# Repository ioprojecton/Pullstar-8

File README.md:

# Pullstar-8
I2C 8 Port Servo Driver

The I2C servo driver board by Surepic© is designed to make connecting motors, sensors and other components to your Arduino,Rasberi Pi-based project as fast and easy as possible.

This board allows your Raspberry Pi,Arduino, etc., to control up to 8 servo motors in a simple way via an I2C connection. Thanks to its I2C capabilities, this board saves the Raspberry Pi's,Arduino`s GPIO pins, allowing you to use them for other purposes.

Each of this board's 8 servo motor GPIO pin headers has been spaced out to the standard 3-pin servo pinout (ground, 5V, signal) to make it easier to attach your servo motors and can supply up to 1.25A to each of 8 outputs.

This driver includes headers to connect to a Raspberry Pi,Arduino , so there is no need for soldering to make it up and running.

Using the onboard jumpers for power selection, the input power can be supplied via Arduino's,Rasberi Pi`s regulated voltage, or a completely separate power supply attached to the board's 2.1mm barrel jack. This feature makes this board ideal if you are connecting multiple servos!

Compared to other servo drivers this board offers:
  Independant power control(ON/OFF) to each outputs via i2c.
  Independant duty cycle control to each outputs via i2c.
  Adjustible frequency to up to 1.6khz.
  1.25A per output when powered from external supply.
  LEDs on each output providing feedback if output is ON or OFF.
  2 selectible power sources selectible with jumpers and with led status indicators.
  Onboard voltage regulator (input 6-7v 3A recommended), when barrel jack is used.
  Open collector outputs on power pins.
  I2C addressess are selectable with jumpers for both onboard ics.
  Fully compatible with fast mode I2C 400kbits/s.
  Each board is fully tested before shipping.
  
=========================

Features:

•16 PWM channels, controllable over I2C
•2.1mm industry standard barrel jack port
•Contain an I2C-controlled PWM ic with a built-in clock
•12-bit resolution for each output - for servos(4us at 60hz)
•Controls up to 8 servos
.Dual power inputs (selectible with jumpers).
.Onboard low noise low ripple regulator.
.115 x 105mm size
.Feedback LEDs on each output
.Independant power control to each output

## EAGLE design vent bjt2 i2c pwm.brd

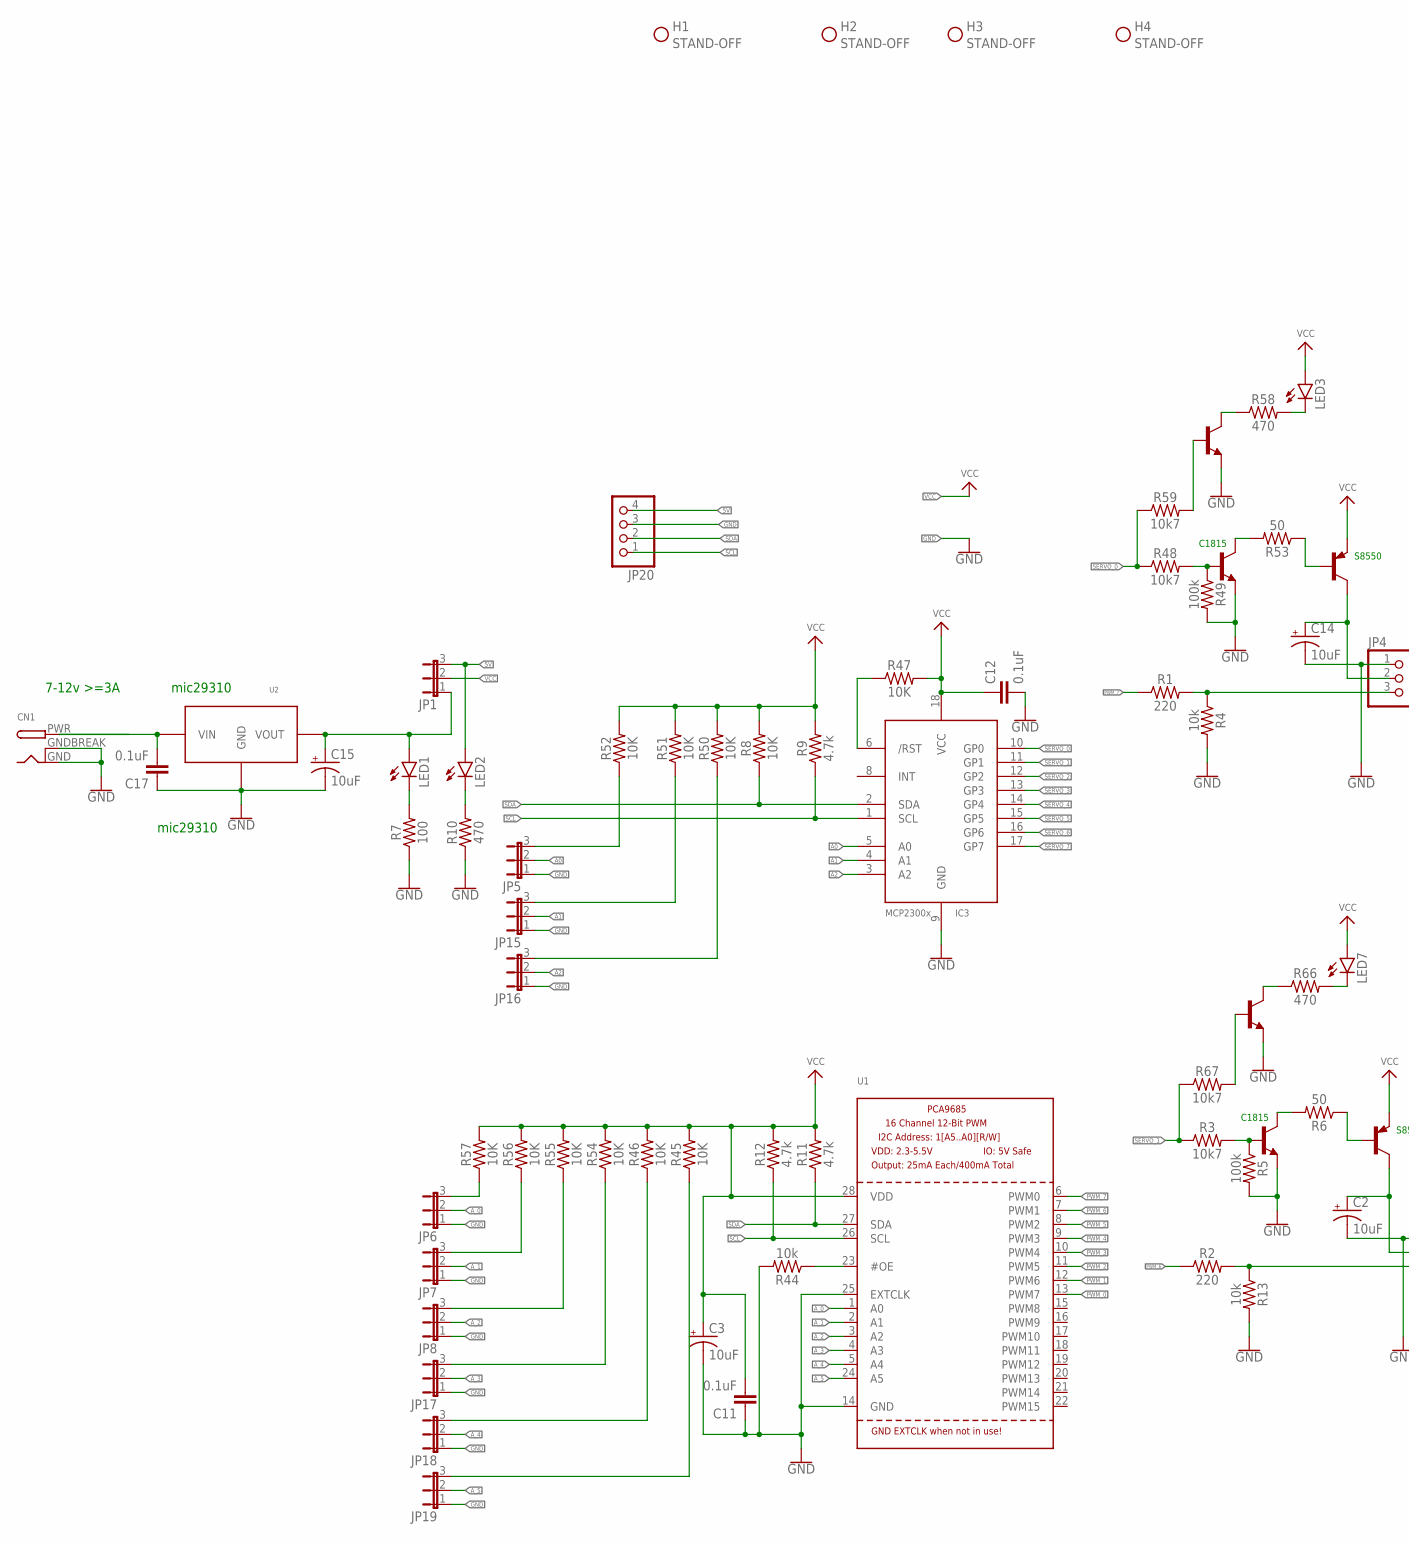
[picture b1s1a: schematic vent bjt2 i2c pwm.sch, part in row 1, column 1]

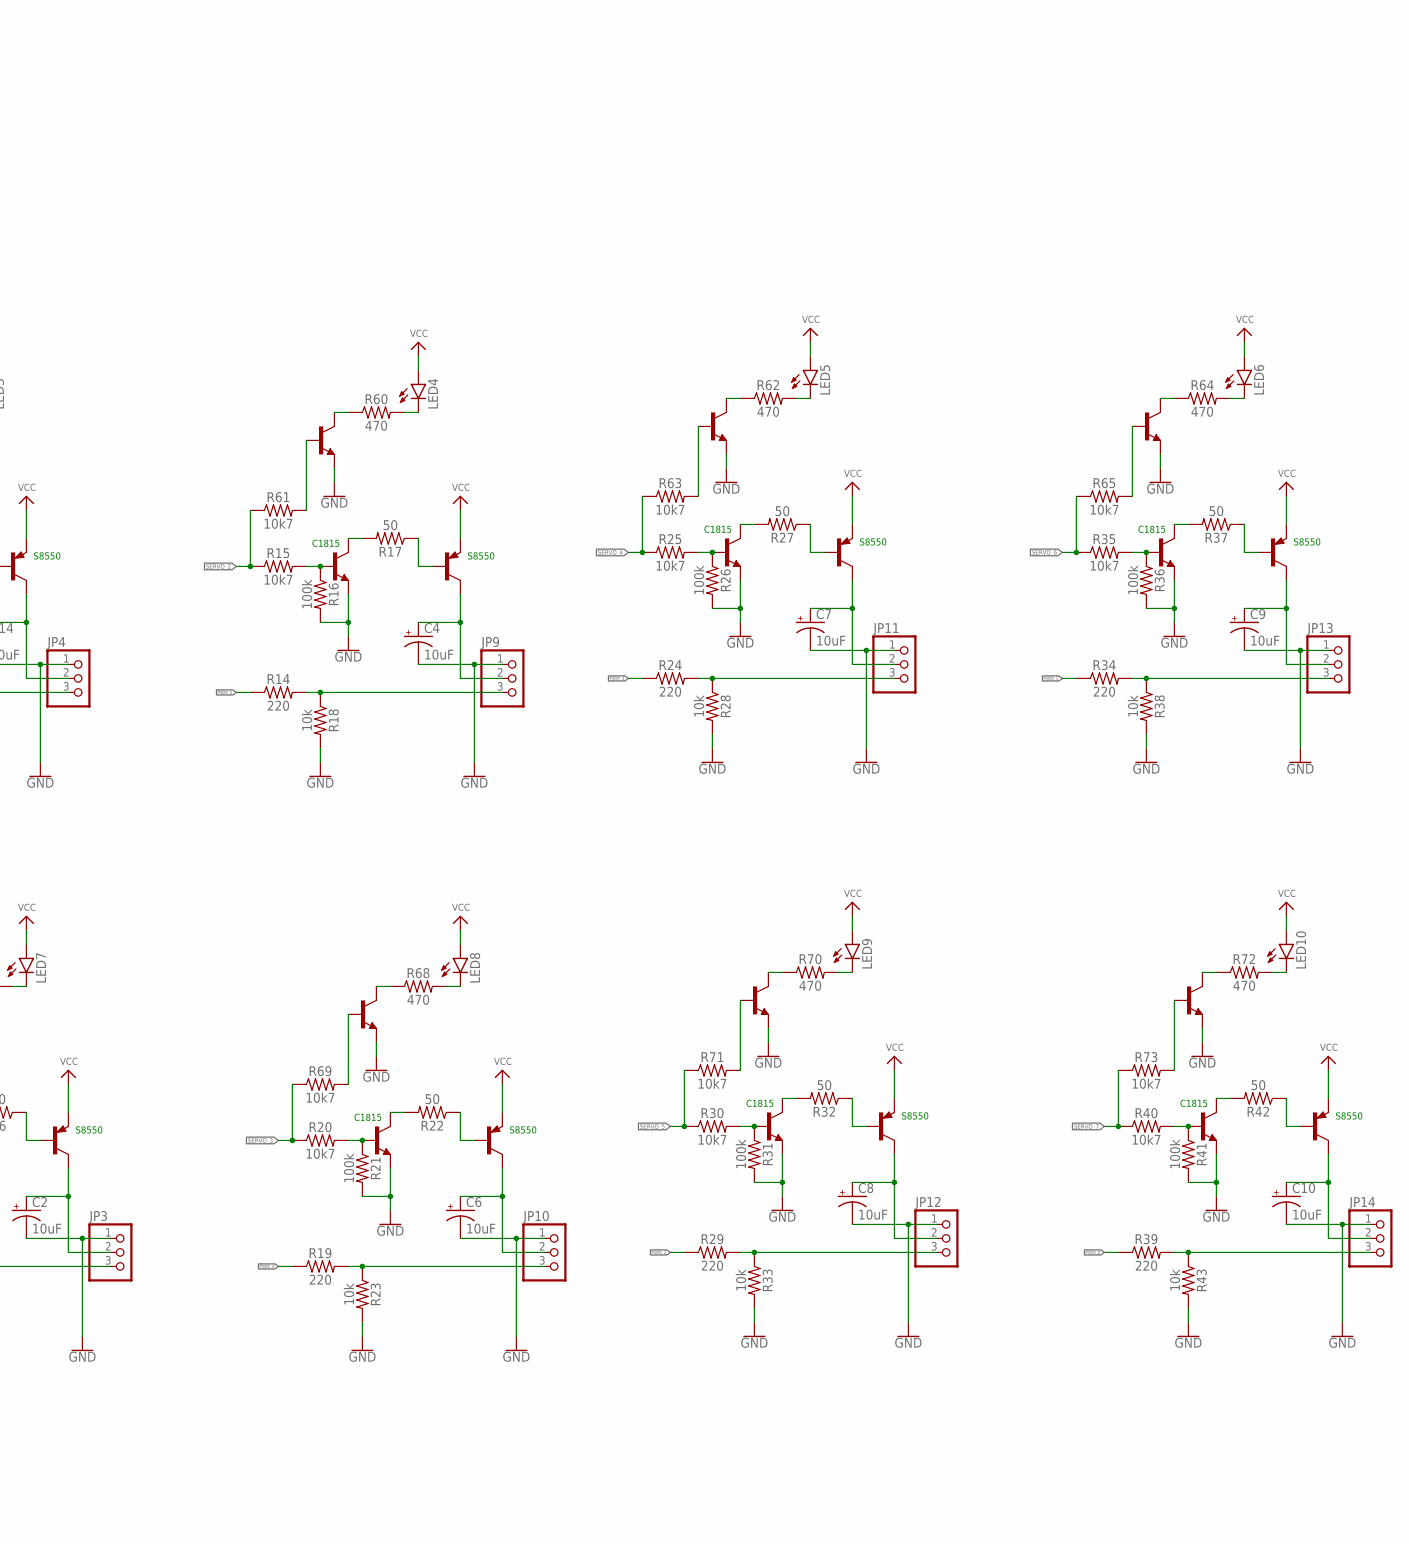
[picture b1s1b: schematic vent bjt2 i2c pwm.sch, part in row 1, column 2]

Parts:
C2, C3, C4, C6, C7, C8, C9, C10, C14, C15: 10uF; CPOL-RADIAL-2.5MM-5MM
C11, C12, C17: 0.1uF; CAP-PTH-SMALL-KIT
CN1: DCBARRELPTH; DCJACK_2MM_PTH
H1, H2, H3, H4: STAND-OFF
IC3: MCP23008/P; DIL18
JP1, JP5, JP6, JP7, JP8, JP15, JP16, JP17, JP18, JP19: JP2E; JP2
JP3, JP4, JP9, JP10, JP11, JP12, JP13, JP14: PINHD-1X3; 1X03
JP20: PINHD-1X4; 1X04
LED1, LED2, LED3, LED4, LED5, LED6, LED7, LED8, LED9, LED10: LEDCHIPLED_1206; CHIPLED_1206
Q1, Q2, Q3, Q4, Q5, Q6, Q7, Q9: 2N2907; TO92-EBC-OVAL
R1, R2, R14, R19, R24, R29, R34, R39: 220; AXIAL-0.3
R3, R15, R20, R25, R30, R35, R40, R48, R59, R61, R63, R65, R67, R69, R71, R73: 10k7; AXIAL-0.3
R4, R13, R18, R23, R28, R33, R38, R43, R44: 10k; AXIAL-0.3
R5, R16, R21, R26, R31, R36, R41, R49: 100k; AXIAL-0.3
R6, R17, R22, R27, R32, R37, R42, R53: 50; AXIAL-0.3
R7: 100; AXIAL-0.3
R8, R45, R46, R47, R50, R51, R52, R54, R55, R56, R57: 10K; AXIAL-0.3
R9, R11, R12: 4.7k; AXIAL-0.3
R10, R58, R60, R62, R64, R66, R68, R70, R72: 470; AXIAL-0.3
T1, T2, T3, T4, T5, T6, T7, T9: 2SC1815; TO92-ECB
U1: PCA9685; TSSOP28
U2: MIC29310_TO-263; TO263-3
U3, U4, U5, U6, U7, U8, U9, U10: S9018; TO92-EBC

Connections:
5V: JP1.3, JP20.4, LED2.A
5V_REG: C15.1 (+), JP1.1, LED1.A, U2.3 (VOUT)
A0: IC3.5 (A0), JP5.2
A1: IC3.4 (A1), JP15.2
A2: IC3.3 (A2), JP16.2
A_0: JP6.2, U1.1 (A0)
A_1: JP7.2, U1.2 (A1)
A_2: JP8.2, U1.3 (A2)
A_3: JP17.2, U1.4 (A3)
A_4: JP18.2, U1.5 (A4)
A_5: JP19.2, U1.24 (A5)
GND: C2.2 (-), C3.2 (-), C4.2 (-), C6.2 (-), C7.2 (-), C8.2 (-), C9.2 (-), C10.2 (-), C11.1, C12.2, C14.2 (-), C15.2 (-), C17.1, CN1.GND, CN1.GNDBREAK, IC3.9 (GND), JP3.1, JP4.1, JP5.1, JP6.1, JP7.1, JP8.1, JP9.1, JP10.1, JP11.1, JP12.1, JP13.1, JP14.1, JP15.1, JP16.1, JP17.1, JP18.1, JP19.1, JP20.3, R4.P$2 (2), R5.P$2 (2), R7.P$1 (1), R10.P$1 (1), R13.P$2 (2), R16.P$2 (2), R18.P$2 (2), R21.P$2 (2), R23.P$2 (2), R26.P$2 (2), R28.P$2 (2), R31.P$2 (2), R33.P$2 (2), R36.P$2 (2), R38.P$2 (2), R41.P$2 (2), R43.P$2 (2), R44.P$2 (2), R49.P$2 (2), T1.E, T2.E, T3.E, T4.E, T5.E, T6.E, T7.E, T9.E, U1.14 (GND), U1.25 (EXTCLK), U2.2 (GND), U2.TAB (GND), U3.E, U4.E, U5.E, U6.E, U7.E, U8.E, U9.E, U10.E
unnamed: JP4.3, R1.P$2 (2), R4.P$1 (1)
unnamed: JP3.3, R2.P$2 (2), R13.P$1 (1)
unnamed: Q9.B, R53.P$1 (1)
unnamed: R3.P$2 (2), R5.P$1 (1), T1.B
unnamed: R6.P$2 (2), T1.C
unnamed: JP8.3, R55.P$1 (1)
unnamed: C2.1 (+), JP3.2, Q1.C
unnamed: C17.2, CN1.PWR, U2.1 (VIN)
unnamed: Q1.B, R6.P$1 (1)
unnamed: JP9.3, R14.P$2 (2), R18.P$1 (1)
unnamed: JP6.3, R57.P$1 (1)
unnamed: JP7.3, R56.P$1 (1)
unnamed: R44.P$1 (1), U1.23 (#OE)
unnamed: LED1.C, R7.P$2 (2)
unnamed: LED2.C, R10.P$2 (2)
unnamed: R58.P$1 (1), U3.C
unnamed: JP17.3, R54.P$1 (1)
unnamed: JP18.3, R46.P$1 (1)
unnamed: R15.P$2 (2), R16.P$1 (1), T2.B
unnamed: R17.P$2 (2), T2.C
unnamed: C4.1 (+), JP9.2, Q2.C
unnamed: Q2.B, R17.P$1 (1)
unnamed: JP10.3, R19.P$2 (2), R23.P$1 (1)
unnamed: R20.P$2 (2), R21.P$1 (1), T3.B
unnamed: R22.P$2 (2), T3.C
unnamed: C6.1 (+), JP10.2, Q3.C
unnamed: Q3.B, R22.P$1 (1)
unnamed: JP11.3, R24.P$2 (2), R28.P$1 (1)
unnamed: R25.P$2 (2), R26.P$1 (1), T4.B
unnamed: R27.P$2 (2), T4.C
unnamed: C7.1 (+), JP11.2, Q4.C
unnamed: Q4.B, R27.P$1 (1)
unnamed: JP12.3, R29.P$2 (2), R33.P$1 (1)
unnamed: R30.P$2 (2), R31.P$1 (1), T5.B
unnamed: R32.P$2 (2), T5.C
unnamed: C8.1 (+), JP12.2, Q5.C
unnamed: Q5.B, R32.P$1 (1)
unnamed: JP13.3, R34.P$2 (2), R38.P$1 (1)
unnamed: R35.P$2 (2), R36.P$1 (1), T6.B
unnamed: R37.P$2 (2), T6.C
unnamed: C9.1 (+), JP13.2, Q6.C
unnamed: Q6.B, R37.P$1 (1)
unnamed: JP19.3, R45.P$1 (1)
unnamed: JP5.3, R52.P$1 (1)
unnamed: JP15.3, R51.P$1 (1)
unnamed: JP16.3, R50.P$1 (1)
unnamed: IC3.6 (/RST), R47.P$1 (1)
unnamed: JP14.3, R39.P$2 (2), R43.P$1 (1)
unnamed: R48.P$2 (2), R49.P$1 (1), T9.B
unnamed: R53.P$2 (2), T9.C
unnamed: R40.P$2 (2), R41.P$1 (1), T7.B
unnamed: C14.1 (+), JP4.2, Q9.C
unnamed: R42.P$2 (2), T7.C
unnamed: C10.1 (+), JP14.2, Q7.C
unnamed: Q7.B, R42.P$1 (1)
unnamed: LED3.C, R58.P$2 (2)
unnamed: R59.P$2 (2), U3.B
unnamed: R60.P$1 (1), U4.C
unnamed: LED4.C, R60.P$2 (2)
unnamed: R61.P$2 (2), U4.B
unnamed: R62.P$1 (1), U5.C
unnamed: LED5.C, R62.P$2 (2)
unnamed: R63.P$2 (2), U5.B
unnamed: R64.P$1 (1), U6.C
unnamed: LED6.C, R64.P$2 (2)
unnamed: R65.P$2 (2), U6.B
unnamed: R66.P$1 (1), U7.C
unnamed: LED7.C, R66.P$2 (2)
unnamed: R67.P$2 (2), U7.B
unnamed: R68.P$1 (1), U8.C
unnamed: LED8.C, R68.P$2 (2)
unnamed: R69.P$2 (2), U8.B
unnamed: R70.P$1 (1), U9.C
unnamed: LED9.C, R70.P$2 (2)
unnamed: R71.P$2 (2), U9.B
unnamed: R72.P$1 (1), U10.C
unnamed: LED10.C, R72.P$2 (2)
unnamed: R73.P$2 (2), U10.B
PWM_0: R39.P$1 (1), U1.13 (PWM7)
PWM_1: R34.P$1 (1), U1.12 (PWM6)
PWM_2: R29.P$1 (1), U1.11 (PWM5)
PWM_3: R24.P$1 (1), U1.10 (PWM4)
PWM_4: R19.P$1 (1), U1.9 (PWM3)
PWM_5: R14.P$1 (1), U1.8 (PWM2)
PWM_6: R2.P$1 (1), U1.7 (PWM1)
PWM_7: R1.P$1 (1), U1.6 (PWM0)
SCL: IC3.1 (SCL), JP20.1, R9.P$1 (1), R12.P$1 (1), U1.26 (SCL)
SDA: IC3.2 (SDA), JP20.2, R8.P$1 (1), R11.P$1 (1), U1.27 (SDA)
SERVO_0: IC3.10 (GP0), R48.P$1 (1), R59.P$1 (1)
SERVO_1: IC3.11 (GP1), R3.P$1 (1), R67.P$1 (1)
SERVO_2: IC3.12 (GP2), R15.P$1 (1), R61.P$1 (1)
SERVO_3: IC3.13 (GP3), R20.P$1 (1), R69.P$1 (1)
SERVO_4: IC3.14 (GP4), R25.P$1 (1), R63.P$1 (1)
SERVO_5: IC3.15 (GP5), R30.P$1 (1), R71.P$1 (1)
SERVO_6: IC3.16 (GP6), R35.P$1 (1), R65.P$1 (1)
SERVO_7: IC3.17 (GP7), R40.P$1 (1), R73.P$1 (1)
VCC: C3.1 (+), C11.2, C12.1, IC3.18 (VCC), JP1.2, LED3.A, LED4.A, LED5.A, LED6.A, LED7.A, LED8.A, LED9.A, LED10.A, Q1.E, Q2.E, Q3.E, Q4.E, Q5.E, Q6.E, Q7.E, Q9.E, R8.P$2 (2), R9.P$2 (2), R11.P$2 (2), R12.P$2 (2), R45.P$2 (2), R46.P$2 (2), R47.P$2 (2), R50.P$2 (2), R51.P$2 (2), R52.P$2 (2), R54.P$2 (2), R55.P$2 (2), R56.P$2 (2), R57.P$2 (2), U1.28 (VDD)

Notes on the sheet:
7-12v >=3A
C1815
S8550
mic29310

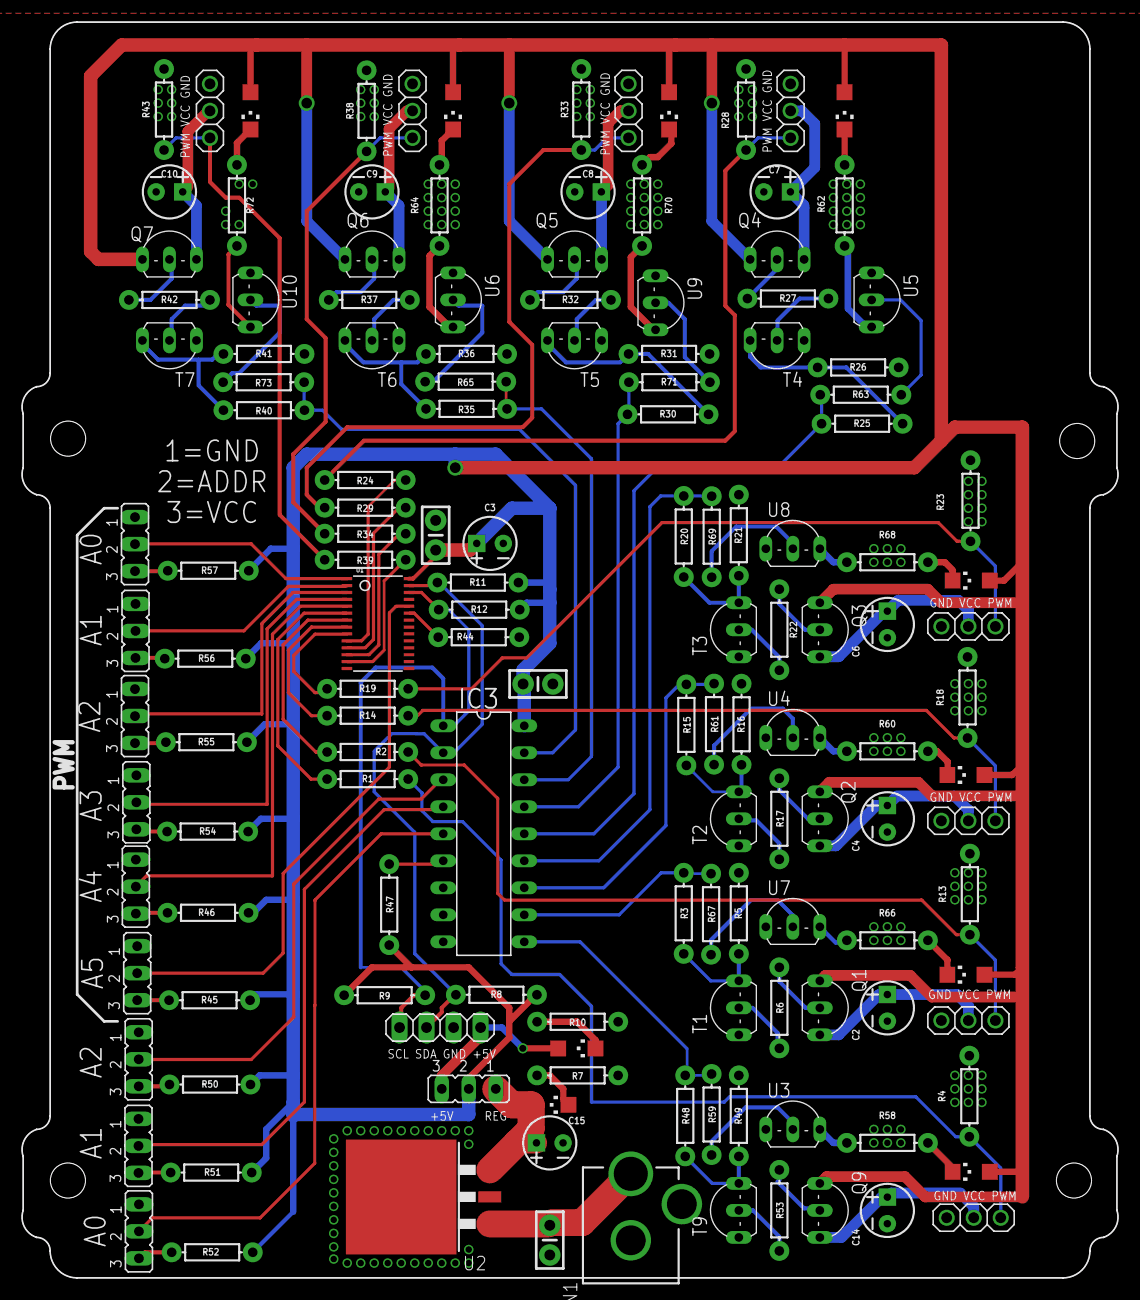
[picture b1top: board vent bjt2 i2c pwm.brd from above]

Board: 2 copper layers, 103.1 x 118.1 mm, 147 parts (0 on the bottom side), 109 nets.

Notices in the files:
parts and their libraries:
SparkFun-Capacitors: Licensing: Creative Commons ShareAlike 4.0 International - https://creativecommons.org/licenses/by-sa/4.0
